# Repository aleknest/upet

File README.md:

# upet

[Відео роботи верстата](https://youtu.be/OY4By4eS6UQ)

[Список комплектуючих верстата](./bom/bom_machine.txt).

[Список комплектуючих підтримувача бобіни з лентою](./bom/bom_spool.txt).

[Список комплектуючих підтримувача бобіни з філаментом для принтера](./bom/bom_printer.txt).

Бобіни для порізаної ленти: https://www.thingiverse.com/thing:1848206

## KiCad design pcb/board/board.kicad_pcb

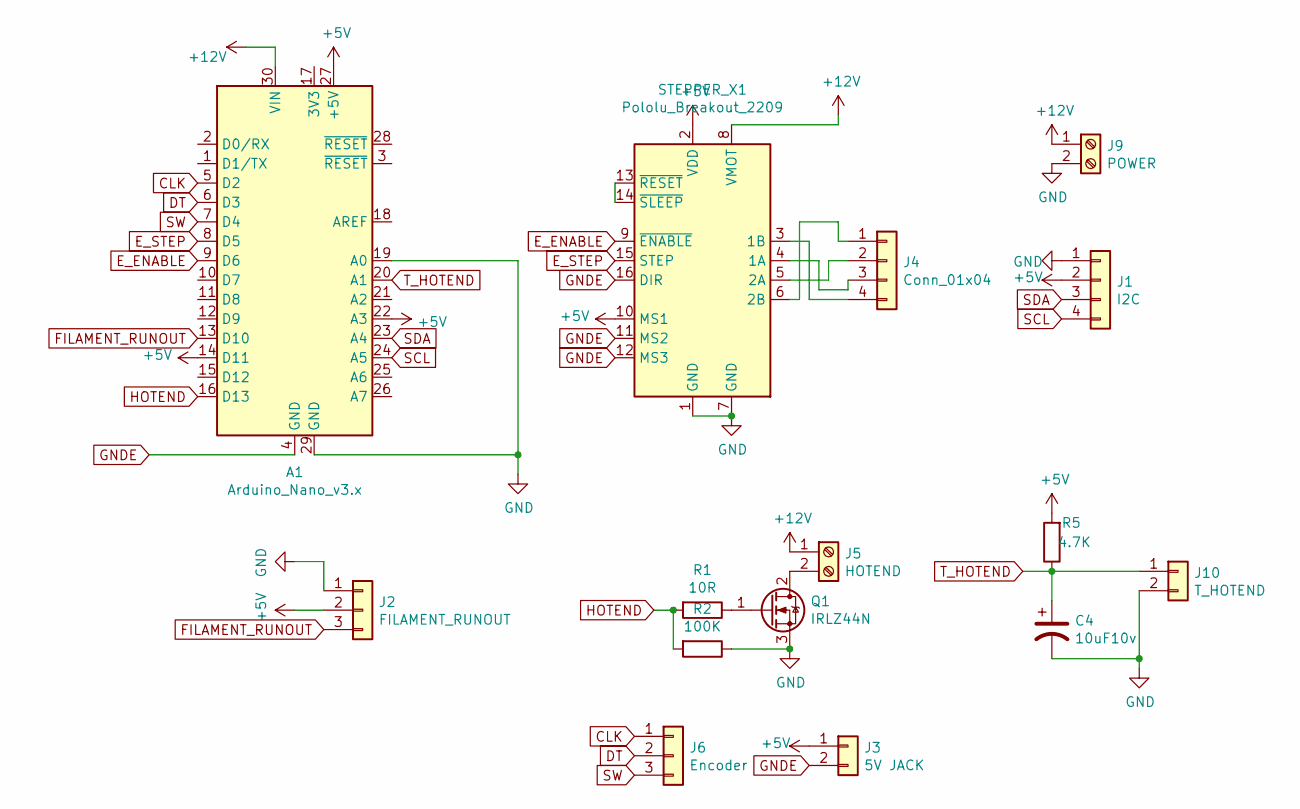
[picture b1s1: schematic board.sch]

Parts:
A1: Arduino_Nano_v3.x; Arduino_Nano
C4: 10uF10v; CP_EIA-3216-12_Kemet-S_Pad1.58x1.35mm_HandSolder
J1: I2C; PinHeader_1x04_P2.54mm_Vertical
J2: FILAMENT_RUNOUT; PinHeader_1x03_P2.54mm_Vertical
J3: 5V JACK; PinHeader_1x02_P2.54mm_Vertical
J4: Conn_01x04; PinHeader_1x04_P2.54mm_Vertical
J5: HOTEND; TerminalBlock_Phoenix_MKDS-1,5-2_1x02_P5.00mm_Horizontal
J6: Encoder; PinHeader_1x03_P2.54mm_Vertical
J9: POWER; TerminalBlock_Phoenix_MKDS-1,5-2_1x02_P5.00mm_Horizontal
J10: T_HOTEND; PinHeader_1x02_P2.54mm_Vertical
Q1: IRLZ44N; TO-220-3_Vertical
R1: 10R; R_Axial_DIN0207_L6.3mm_D2.5mm_P7.62mm_Horizontal
R2: 100K; R_Axial_DIN0207_L6.3mm_D2.5mm_P7.62mm_Horizontal
R5: 4.7K; R_Axial_DIN0207_L6.3mm_D2.5mm_P7.62mm_Horizontal
STEPPER_X1: Pololu_Breakout_2209; Pololu_Breakout-16_15.2x20.3mm

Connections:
+5V: A1.14 (D11), A1.22 (A3), A1.27 (+5V), J1.2, J2.2, J3.1, R5.2, STEPPER_X1.2 (VDD), STEPPER_X1.10 (MS1)
+12V: A1.30 (VIN), J5.1, J9.1, STEPPER_X1.8 (VMOT)
CLK: A1.5 (D2), J6.1
DT: A1.6 (D3), J6.2
E_ENABLE: A1.9 (D6), STEPPER_X1.9 (~ENABLE)
E_STEP: A1.8 (D5), STEPPER_X1.15 (STEP)
FILAMENT_RUNOUT: A1.13 (D10), J2.3
GND: A1.19 (A0), A1.29 (GND), C4.2, J1.1, J2.1, J9.2, J10.2, Q1.3 (S), R2.1, STEPPER_X1.1 (GND), STEPPER_X1.7 (GND)
GNDE: A1.4 (GND), J3.2, STEPPER_X1.11 (MS2), STEPPER_X1.12 (MS3), STEPPER_X1.16 (DIR)
HOTEND: A1.16 (D13), R1.2, R2.2
unnamed: J4.1, STEPPER_X1.6 (2B)
unnamed: J4.2, STEPPER_X1.5 (2A)
unnamed: J4.3, STEPPER_X1.4 (1A)
unnamed: J4.4, STEPPER_X1.3 (1B)
unnamed: J5.2, Q1.2 (D)
unnamed: Q1.1 (G), R1.1
unnamed: STEPPER_X1.13 (~RESET), STEPPER_X1.14 (~SLEEP)
SCL: A1.24 (A5), J1.4
SDA: A1.23 (A4), J1.3
SW: A1.7 (D4), J6.3
T_HOTEND: A1.20 (A1), C4.1, J10.1, R5.1

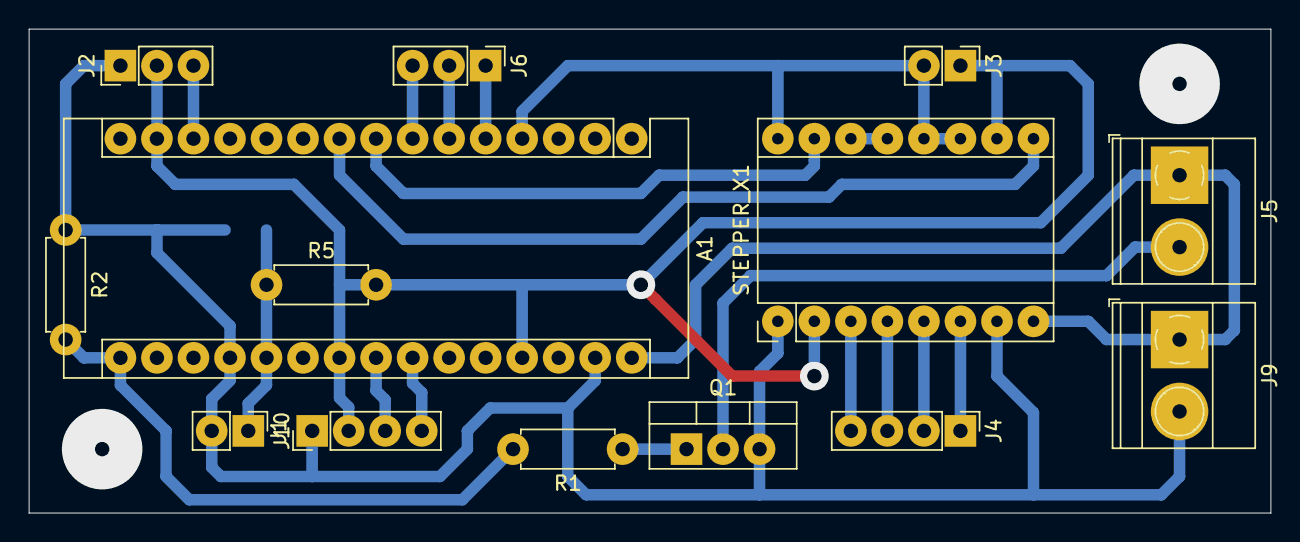
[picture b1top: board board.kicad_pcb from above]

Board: 2 copper layers, 86.4 x 33.7 mm, 15 parts (1 on the bottom side), 21 nets.
